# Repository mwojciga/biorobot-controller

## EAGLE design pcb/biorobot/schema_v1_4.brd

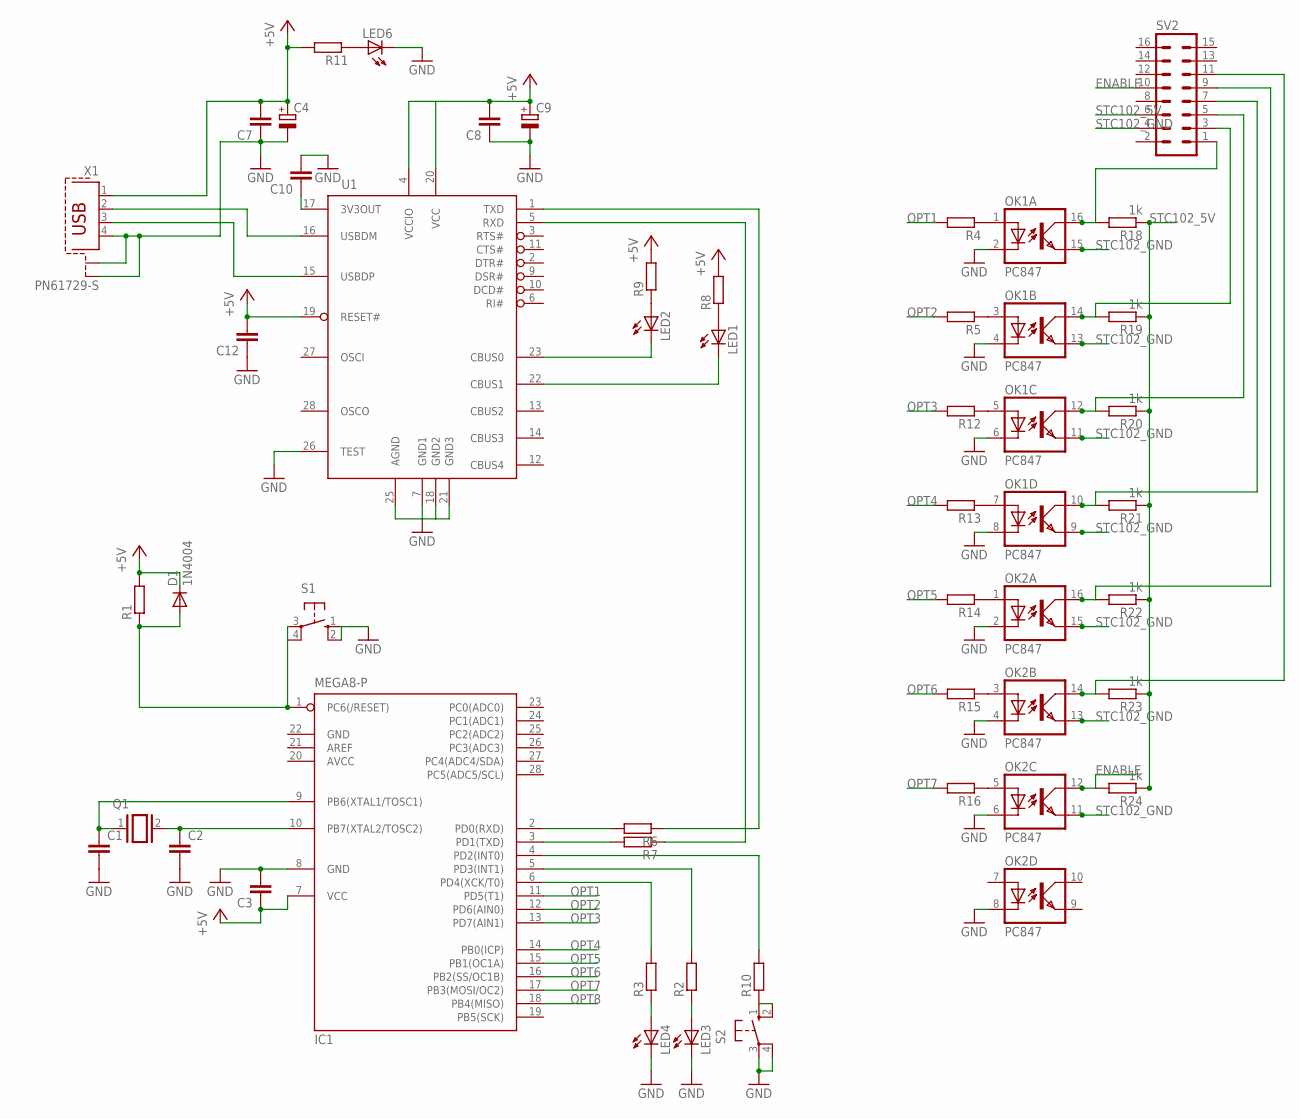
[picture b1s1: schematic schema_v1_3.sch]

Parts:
C1, C2, C3: C-EUC0805; C0805
C4, C9: CPOL-EUE2.5-5; E2,5-5
C7, C8, C10, C12: C-EU025-025X050; C025-025X050
D1: 1N4004; DO41-10
IC1: MEGA8-P; DIL28-3
LED1, LED2, LED3, LED4, LED6: LED3MM
OK1, OK2: PC847; DIL16
Q1: XTAL; Q
R1, R2, R3, R4, R5, R10, R12, R13, R14, R15, R16: R-EU_0207/10; 0207/10
R6, R7, R8, R9, R11: R-EU_M1206; M1206
R18, R19, R20, R21, R22, R23, R24: 1k; 0207/10
S1, S2: 10-XX; B3F-10XX
SV2: MA08-2
U1: FT232RL; SSOP28DB
X1: PN61729-S

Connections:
AVCC: IC1.20 (AVCC)
ENABLE: OK2.12 (COL), R24.2, SV2.10
GND: C1.2, C2.2, C3.2, C4.-, C7.1, C8.1, C9.-, C10.2, C12.1, IC1.8 (GND), IC1.22 (GND), LED3.K (C), LED4.K (C), LED6.K (C), OK1.2 (C), OK1.4 (C), OK1.6 (C), OK1.8 (C), OK2.2 (C), OK2.4 (C), OK2.6 (C), OK2.8 (C), S1.1 (S), S1.2 (S1), S2.3, S2.4 (P1), U1.7 (GND1), U1.18 (GND2), U1.21 (GND3), U1.25 (AGND), U1.26 (TEST), X1.4, X1.S1, X1.S2
unnamed: C2.1, IC1.10 (PB7(XTAL2/TOSC2)), Q1.2
unnamed: C1.1, IC1.9 (PB6(XTAL1/TOSC1)), Q1.1
unnamed: IC1.6 (PD4(XCK/T0)), R3.2
unnamed: IC1.4 (PD2(INT0)), R10.2
unnamed: LED3.A, R2.1
unnamed: LED4.A, R3.1
unnamed: R10.1, S2.1 (S), S2.2 (S1)
unnamed: OK1.16 (COL), R18.2, SV2.1
unnamed: IC1.5 (PD3(INT1)), R2.2
unnamed: OK1.14 (COL), R19.2, SV2.3
unnamed: OK1.12 (COL), R20.2, SV2.5
unnamed: OK1.10 (COL), R21.2, SV2.7
unnamed: OK2.16 (COL), R22.2, SV2.9
unnamed: OK2.14 (COL), R23.2, SV2.11
unnamed: LED2.K (C), U1.23 (CBUS0)
unnamed: LED6.A, R11.1
unnamed: U1.16 (USBDM), X1.2
unnamed: U1.15 (USBDP), X1.3
unnamed: C10.1, U1.17 (3V3OUT)
unnamed: LED1.A, R8.1
unnamed: LED2.A, R9.1
unnamed: LED1.K (C), U1.22 (CBUS1)
unnamed: R6.1, U1.1 (TXD)
unnamed: IC1.2 (PD0(RXD)), R6.2
unnamed: IC1.3 (PD1(TXD)), R7.2
unnamed: R7.1, U1.5 (RXD)
unnamed: OK1.1 (A), R4.1
unnamed: OK1.3 (A), R5.1
unnamed: OK1.5 (A), R12.1
unnamed: OK1.7 (A), R13.1
unnamed: OK2.1 (A), R14.1
unnamed: OK2.3 (A), R15.1
unnamed: OK2.5 (A), R16.1
OPT1: IC1.11 (PD5(T1)), R4.2
OPT2: IC1.12 (PD6(AIN0)), R5.2
OPT3: IC1.13 (PD7(AIN1)), R12.2
OPT4: IC1.14 (PB0(ICP)), R13.2
OPT5: IC1.15 (PB1(OC1A)), R14.2
OPT6: IC1.16 (PB2(SS/OC1B)), R15.2
OPT7: IC1.17 (PB3(MOSI/OC2)), R16.2
OPT8: IC1.18 (PB4(MISO))
STC102_5V: R18.1, R19.1, R20.1, R21.1, R22.1, R23.1, R24.1, SV2.6
STC102_GND: OK1.9 (EMIT), OK1.11 (EMIT), OK1.13 (EMIT), OK1.15 (EMIT), OK2.11 (EMIT), OK2.13 (EMIT), OK2.15 (EMIT), SV2.4

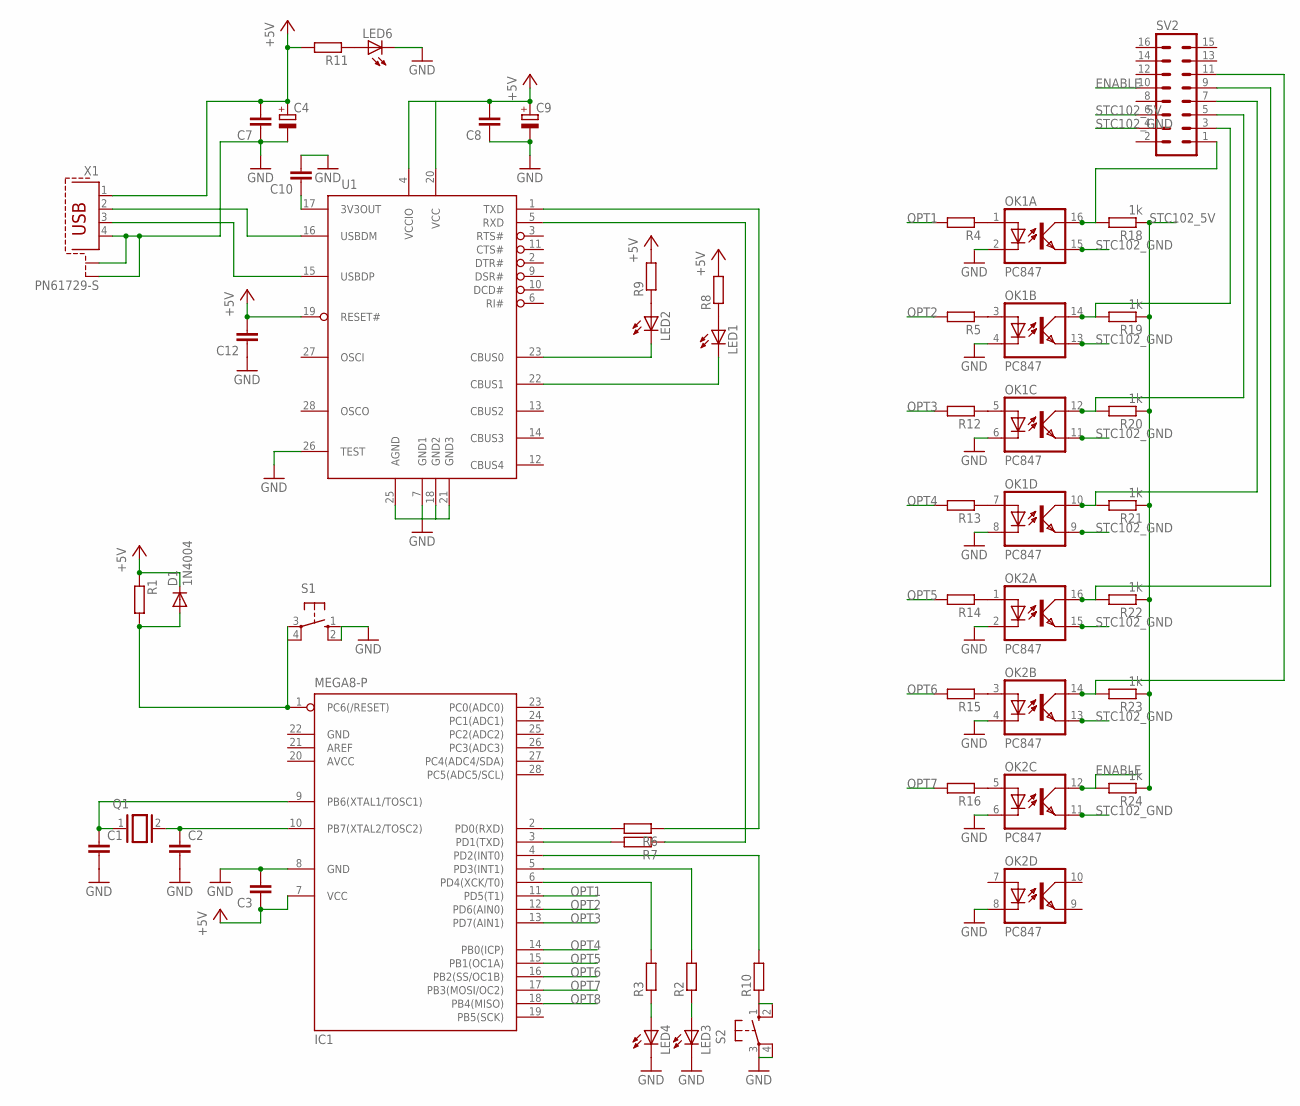
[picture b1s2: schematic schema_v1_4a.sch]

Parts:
C1, C2, C3: C-EUC0805; C0805
C4, C9: CPOL-EUE2.5-5; E2,5-5
C7, C8, C10, C12: C-EU025-025X050; C025-025X050
D1: 1N4004; DO41-10
IC1: MEGA8-P; DIL28-3
LED1, LED2, LED3, LED4, LED6: LED3MM
OK1, OK2: PC847; DIL16
Q1: XTAL; Q
R1, R6, R7, R8, R9, R11: R-EU_M1206; M1206
R2, R3, R4, R5, R10, R12, R13, R14, R15, R16: R-EU_0207/10; 0207/10
R18, R19, R20, R21, R22, R23, R24: 1k; 0207/10
S1, S2: 10-XX; B3F-10XX
SV2: MA08-2
U1: FT232RL; SSOP28DB
X1: PN61729-S

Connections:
AVCC: IC1.20 (AVCC)
ENABLE: OK2.12 (COL), R24.2, SV2.10
GND: C1.2, C2.2, C3.2, C4.-, C7.1, C8.1, C9.-, C10.2, C12.1, IC1.8 (GND), IC1.22 (GND), LED3.K (C), LED4.K (C), LED6.K (C), OK1.2 (C), OK1.4 (C), OK1.6 (C), OK1.8 (C), OK2.2 (C), OK2.4 (C), OK2.6 (C), OK2.8 (C), S1.1 (S), S1.2 (S1), S2.3, S2.4 (P1), U1.7 (GND1), U1.18 (GND2), U1.21 (GND3), U1.25 (AGND), U1.26 (TEST), X1.4, X1.S1, X1.S2
unnamed: C2.1, IC1.10 (PB7(XTAL2/TOSC2)), Q1.2
unnamed: C1.1, IC1.9 (PB6(XTAL1/TOSC1)), Q1.1
unnamed: IC1.6 (PD4(XCK/T0)), R3.2
unnamed: IC1.4 (PD2(INT0)), R10.2
unnamed: LED3.A, R2.1
unnamed: LED4.A, R3.1
unnamed: R10.1, S2.1 (S), S2.2 (S1)
unnamed: OK1.16 (COL), R18.2, SV2.1
unnamed: IC1.5 (PD3(INT1)), R2.2
unnamed: OK1.14 (COL), R19.2, SV2.3
unnamed: OK1.12 (COL), R20.2, SV2.5
unnamed: OK1.10 (COL), R21.2, SV2.7
unnamed: OK2.16 (COL), R22.2, SV2.9
unnamed: OK2.14 (COL), R23.2, SV2.11
unnamed: LED2.K (C), U1.23 (CBUS0)
unnamed: LED6.A, R11.1
unnamed: U1.16 (USBDM), X1.2
unnamed: U1.15 (USBDP), X1.3
unnamed: C10.1, U1.17 (3V3OUT)
unnamed: LED1.A, R8.1
unnamed: LED2.A, R9.1
unnamed: LED1.K (C), U1.22 (CBUS1)
unnamed: R6.1, U1.1 (TXD)
unnamed: IC1.2 (PD0(RXD)), R6.2
unnamed: IC1.3 (PD1(TXD)), R7.2
unnamed: R7.1, U1.5 (RXD)
unnamed: OK1.1 (A), R4.1
unnamed: OK1.3 (A), R5.1
unnamed: OK1.5 (A), R12.1
unnamed: OK1.7 (A), R13.1
unnamed: OK2.1 (A), R14.1
unnamed: OK2.3 (A), R15.1
unnamed: OK2.5 (A), R16.1
OPT1: IC1.11 (PD5(T1)), R4.2
OPT2: IC1.12 (PD6(AIN0)), R5.2
OPT3: IC1.13 (PD7(AIN1)), R12.2
OPT4: IC1.14 (PB0(ICP)), R13.2
OPT5: IC1.15 (PB1(OC1A)), R14.2
OPT6: IC1.16 (PB2(SS/OC1B)), R15.2
OPT7: IC1.17 (PB3(MOSI/OC2)), R16.2
OPT8: IC1.18 (PB4(MISO))
STC102_5V: R18.1, R19.1, R20.1, R21.1, R22.1, R23.1, R24.1, SV2.6
STC102_GND: OK1.9 (EMIT), OK1.11 (EMIT), OK1.13 (EMIT), OK1.15 (EMIT), OK2.11 (EMIT), OK2.13 (EMIT), OK2.15 (EMIT), SV2.4

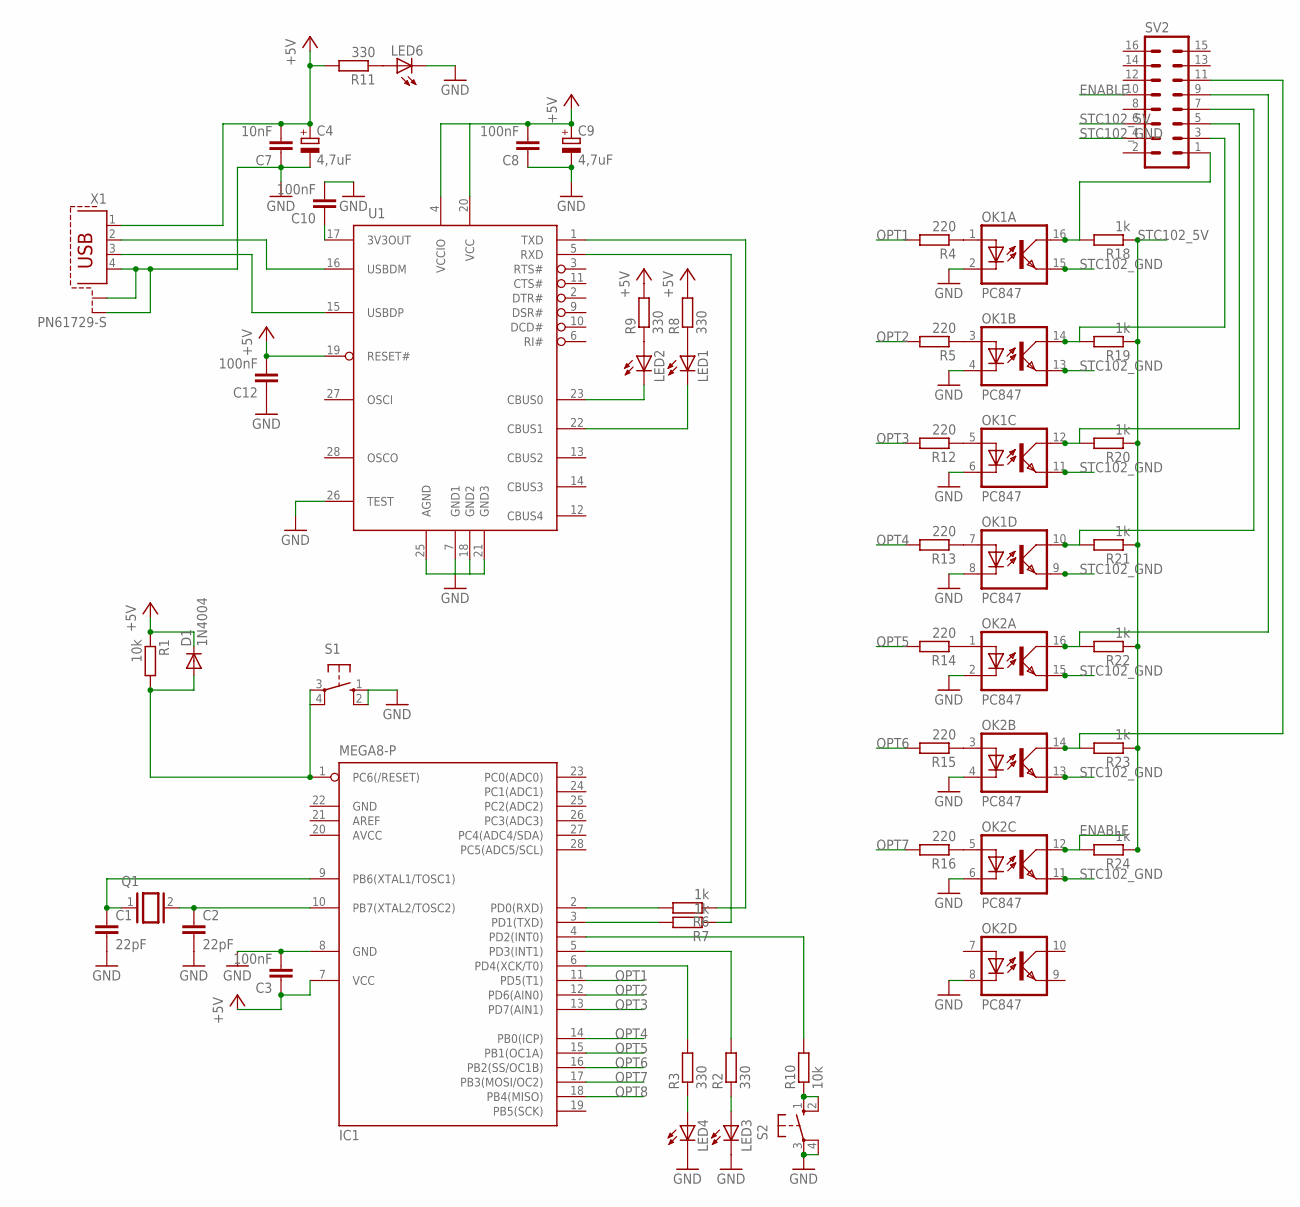
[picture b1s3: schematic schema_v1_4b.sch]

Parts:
C1, C2: 22pF; C0805
C3: 100nF; C0805
C4, C9: 4,7uF; E2,5-5
C7: 10nF; C025-025X050
C8, C10, C12: 100nF; C025-025X050
D1: 1N4004; DO41-10
IC1: MEGA8-P; DIL28-3
LED1, LED2, LED3, LED4, LED6: LED3MM
OK1, OK2: PC847; DIL16
Q1: XTAL; Q
R1: 10k; M1206
R2, R3: 330; 0207/10
R4, R5, R12, R13, R14, R15, R16: 220; 0207/10
R6, R7: 1k; M1206
R8, R9, R11: 330; M1206
R10: 10k; 0207/10
R18, R19, R20, R21, R22, R23, R24: 1k; 0207/10
S1, S2: 10-XX; B3F-10XX
SV2: MA08-2
U1: FT232RL; SSOP28DB
X1: PN61729-S

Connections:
AVCC: IC1.20 (AVCC)
ENABLE: OK2.12 (COL), R24.2, SV2.10
GND: C1.2, C2.2, C3.2, C4.-, C7.1, C8.1, C9.-, C10.2, C12.1, IC1.8 (GND), IC1.22 (GND), LED3.K (C), LED4.K (C), LED6.K (C), OK1.2 (C), OK1.4 (C), OK1.6 (C), OK1.8 (C), OK2.2 (C), OK2.4 (C), OK2.6 (C), OK2.8 (C), S1.1 (S), S1.2 (S1), S2.3, S2.4 (P1), U1.7 (GND1), U1.18 (GND2), U1.21 (GND3), U1.25 (AGND), U1.26 (TEST), X1.4, X1.S1, X1.S2
unnamed: C2.1, IC1.10 (PB7(XTAL2/TOSC2)), Q1.2
unnamed: C1.1, IC1.9 (PB6(XTAL1/TOSC1)), Q1.1
unnamed: IC1.6 (PD4(XCK/T0)), R3.2
unnamed: IC1.4 (PD2(INT0)), R10.2
unnamed: LED3.A, R2.1
unnamed: LED4.A, R3.1
unnamed: R10.1, S2.1 (S), S2.2 (S1)
unnamed: OK1.16 (COL), R18.2, SV2.1
unnamed: IC1.5 (PD3(INT1)), R2.2
unnamed: OK1.14 (COL), R19.2, SV2.3
unnamed: OK1.12 (COL), R20.2, SV2.5
unnamed: OK1.10 (COL), R21.2, SV2.7
unnamed: OK2.16 (COL), R22.2, SV2.9
unnamed: OK2.14 (COL), R23.2, SV2.11
unnamed: LED2.K (C), U1.23 (CBUS0)
unnamed: LED6.A, R11.1
unnamed: U1.16 (USBDM), X1.2
unnamed: U1.15 (USBDP), X1.3
unnamed: C10.1, U1.17 (3V3OUT)
unnamed: LED1.A, R8.1
unnamed: LED2.A, R9.1
unnamed: LED1.K (C), U1.22 (CBUS1)
unnamed: R6.1, U1.1 (TXD)
unnamed: IC1.2 (PD0(RXD)), R6.2
unnamed: IC1.3 (PD1(TXD)), R7.2
unnamed: R7.1, U1.5 (RXD)
unnamed: OK1.1 (A), R4.1
unnamed: OK1.3 (A), R5.1
unnamed: OK1.5 (A), R12.1
unnamed: OK1.7 (A), R13.1
unnamed: OK2.1 (A), R14.1
unnamed: OK2.3 (A), R15.1
unnamed: OK2.5 (A), R16.1
OPT1: IC1.11 (PD5(T1)), R4.2
OPT2: IC1.12 (PD6(AIN0)), R5.2
OPT3: IC1.13 (PD7(AIN1)), R12.2
OPT4: IC1.14 (PB0(ICP)), R13.2
OPT5: IC1.15 (PB1(OC1A)), R14.2
OPT6: IC1.16 (PB2(SS/OC1B)), R15.2
OPT7: IC1.17 (PB3(MOSI/OC2)), R16.2
OPT8: IC1.18 (PB4(MISO))
STC102_5V: R18.1, R19.1, R20.1, R21.1, R22.1, R23.1, R24.1, SV2.6
STC102_GND: OK1.9 (EMIT), OK1.11 (EMIT), OK1.13 (EMIT), OK1.15 (EMIT), OK2.11 (EMIT), OK2.13 (EMIT), OK2.15 (EMIT), SV2.4

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
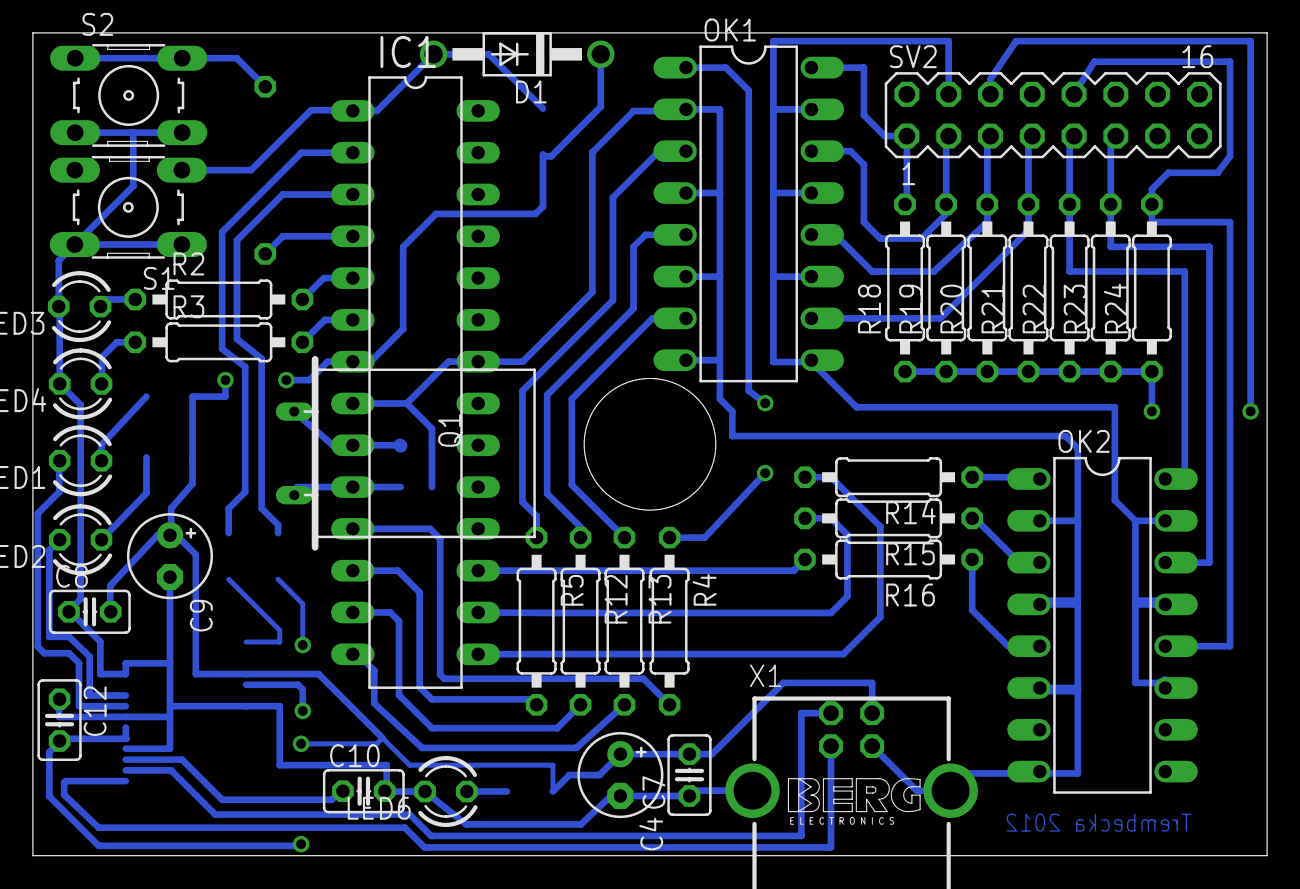
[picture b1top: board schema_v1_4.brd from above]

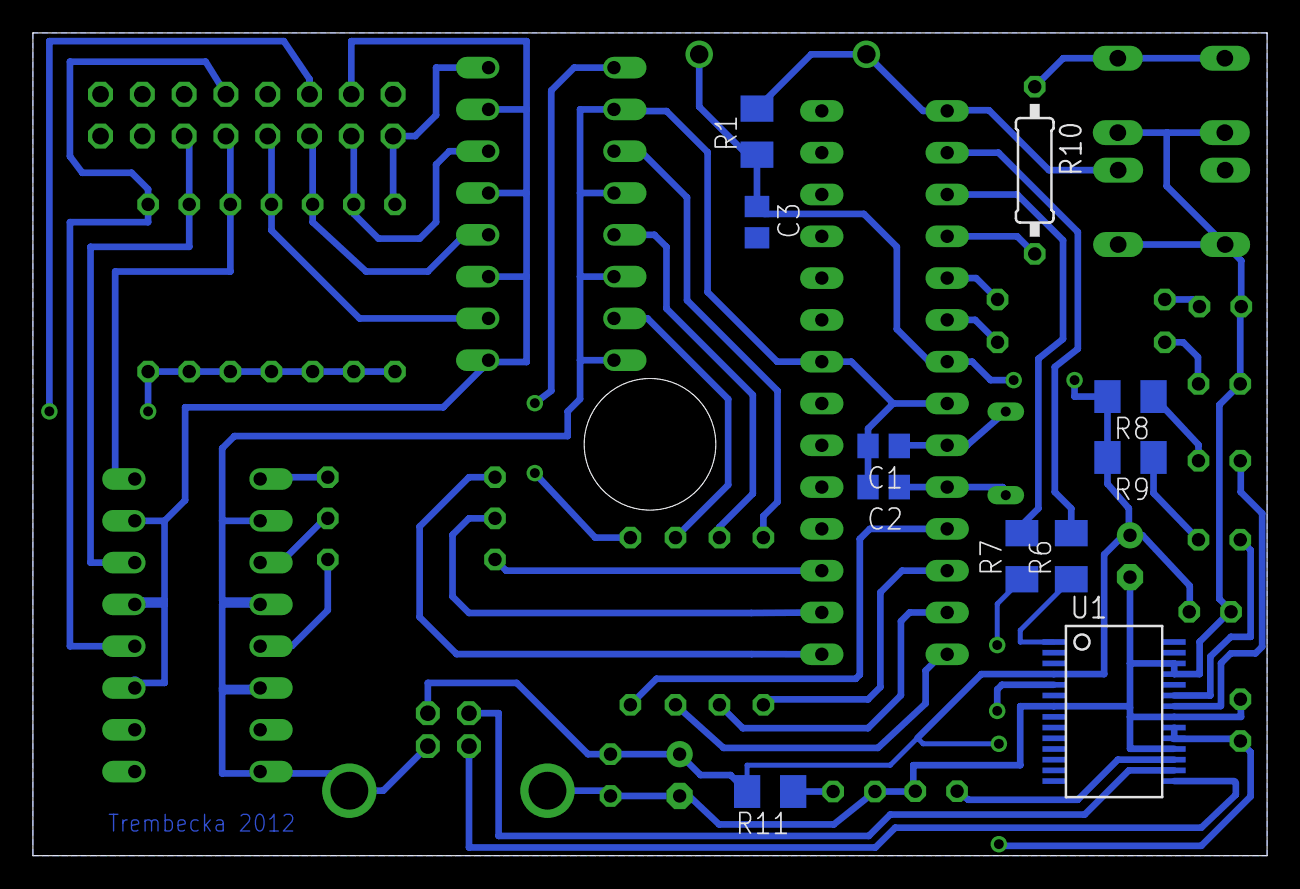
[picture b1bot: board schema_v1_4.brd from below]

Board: 2 copper layers, 75.0 x 50.0 mm, 47 parts (11 on the bottom side), 46 nets.
